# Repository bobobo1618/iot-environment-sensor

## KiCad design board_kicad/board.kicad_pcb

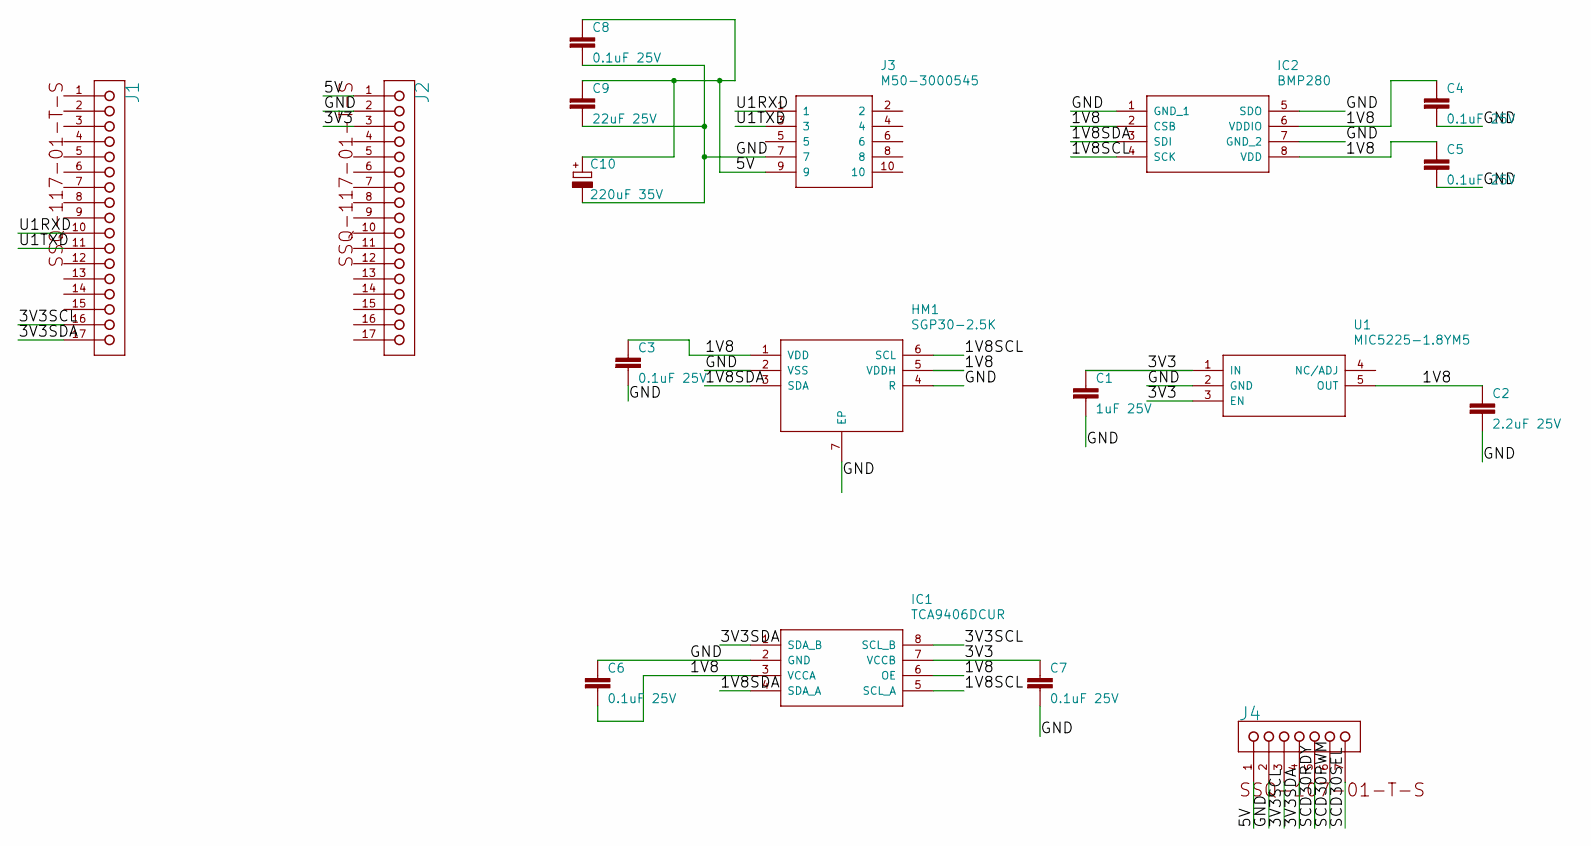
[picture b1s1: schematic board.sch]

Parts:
C1: 1uF 25V; C0402
C2: 2.2uF 25V; C0402
C3, C4, C5, C6, C7, C8: 0.1uF 25V; C0402
C9: 22uF 25V; C0805
C10: 220uF 35V; E5-10,5
HM1: SGP30-2.5K; SON80P245X245X90-7N
IC1: TCA9406DCUR; SOP50P310X90-8N
IC2: BMP280; 8-PIN-METAL-LID-LGA_1
J1, J2: SAMTEC_SSQ-117-01-T-SSAMTEC_SSQ-117-01-T-S_0_0; SAMTEC_SSQ-117-01-T-S_0
J3: M50-3000545; SHDR10W40P127X127_2X5_675X310X
J4: SAMTEC_SSQ-107-01-T-SSAMTEC_SSQ-107-01-T-S_0_0; SAMTEC_SSQ-107-01-T-S_0
U1: MIC5225-1.8YM5; SOT95P280X145-5N

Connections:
/1V8: C2.1, C3.1, C4.1, C5.1, C6.2, HM1.1 (VDD), HM1.5 (VDDH), IC1.3 (VCCA), IC1.6 (OE), IC2.2 (CSB), IC2.6 (VDDIO), IC2.8 (VDD), U1.5 (OUT)
/1V8SCL: HM1.6 (SCL), IC1.5 (SCL_A), IC2.4 (SCK)
/1V8SDA: HM1.3 (SDA), IC1.4 (SDA_A), IC2.3 (SDI)
/3V3: C1.1, C7.1, IC1.7 (VCCB), J2.3, U1.1 (IN), U1.3 (EN)
/3V3SCL: IC1.8 (SCL_B), J1.16, J4.3
/3V3SDA: IC1.1 (SDA_B), J1.17, J4.4
/5V: C8.1, C9.1, C10.+, J2.1, J3.9, J4.1
/GND: C1.2, C2.2, C3.2, C4.2, C5.2, C6.1, C7.2, C8.2, C9.2, C10.-, HM1.2 (VSS), HM1.4 (R), HM1.7 (EP), IC1.2 (GND), IC2.1 (GND_1), IC2.5 (SDO), IC2.7 (GND_2), J2.2, J3.7, J4.2, U1.2 (GND)
/SCD30PWM: J4.6
/SCD30RDY: J4.5
/SCD30SEL: J4.7
/U1RXD: J1.10, J3.1
/U1TXD: J1.11, J3.3

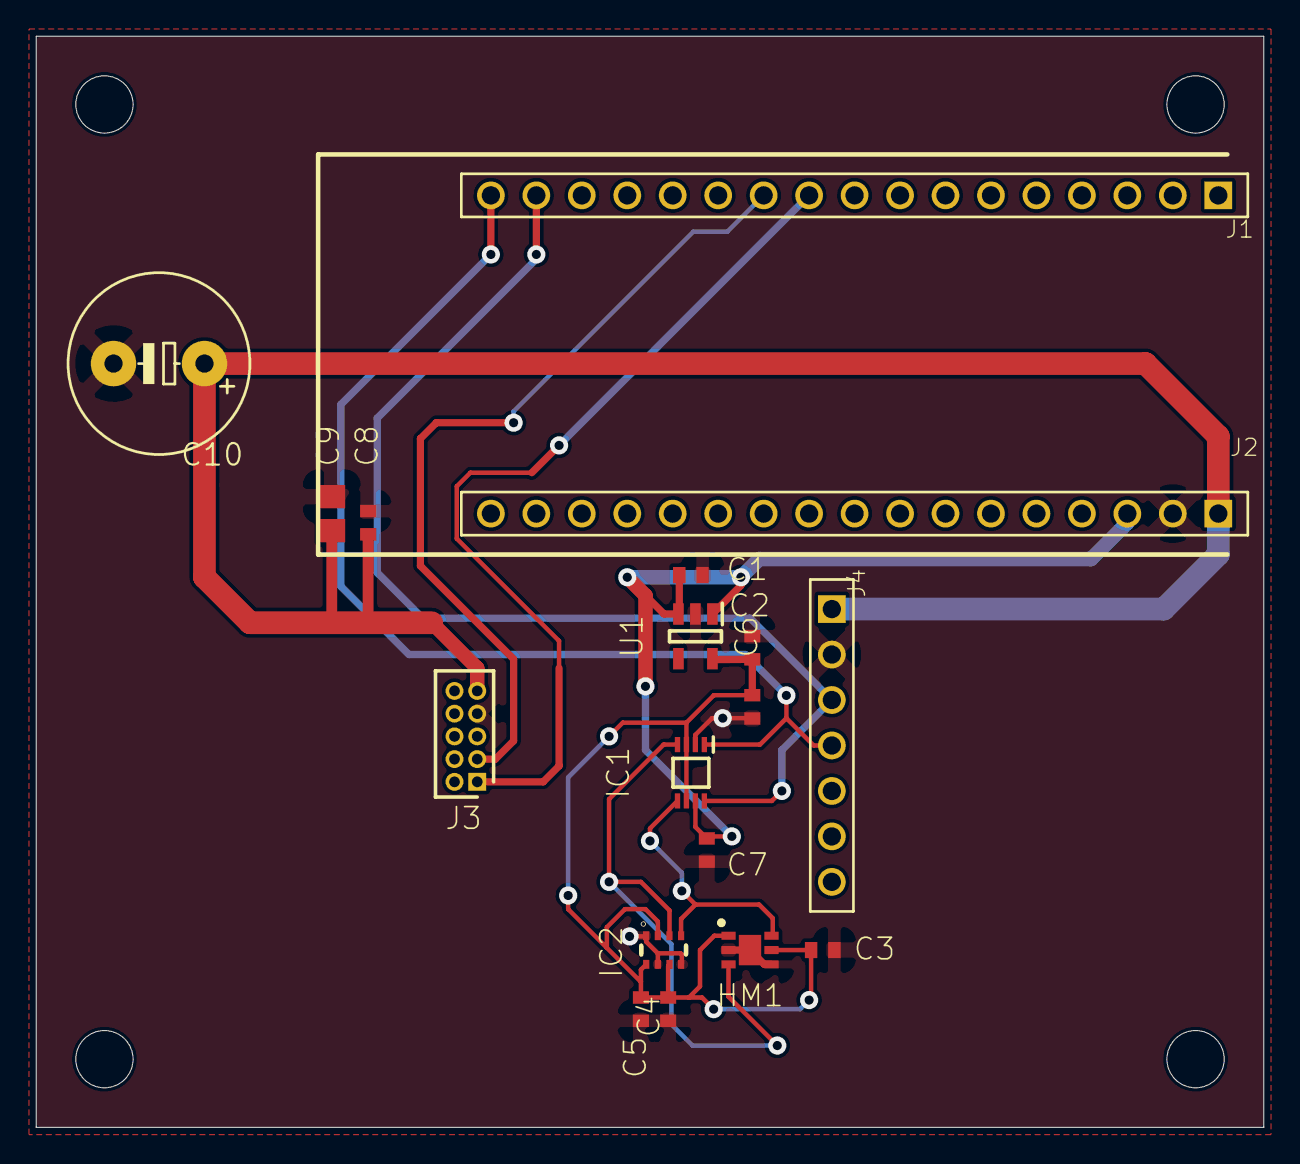
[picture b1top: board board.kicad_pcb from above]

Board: 2 copper layers, 68.6 x 61.0 mm, 22 parts (0 on the bottom side), 10 nets.

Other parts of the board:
@HOLE0, @HOLE1, @HOLE2, @HOLE3: (no value)

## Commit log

2020-02-19 Add board
2020-02-19 Add Kicad conversion
